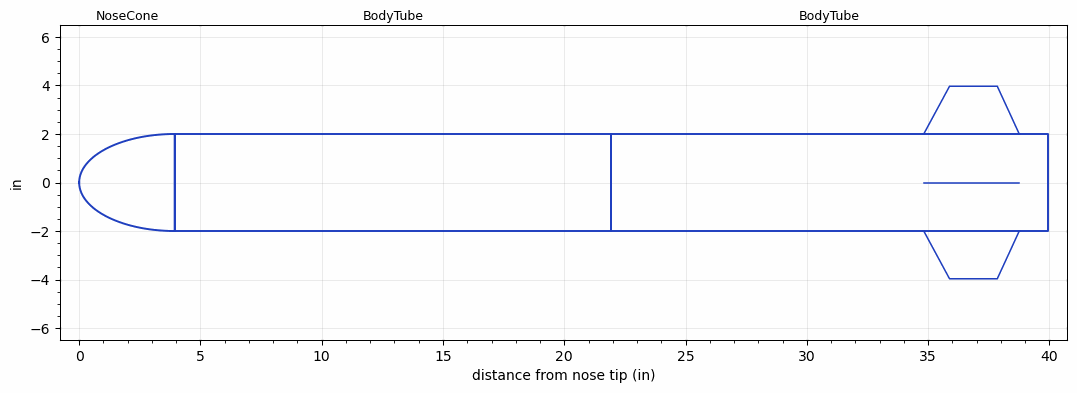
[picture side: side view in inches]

<RASAeroDocument>
 <FileVersion>2</FileVersion>
 <RocketDesign>
  <NoseCone>
   <Length>3.937</Length>
   <Diameter>4</Diameter>
   <Shape>Elliptical</Shape>
   <Location>0</Location>
  </NoseCone>
  <BodyTube>
   <Length>18</Length>
   <Diameter>4</Diameter>
   <Location>3.937</Location>
  </BodyTube>
  <BodyTube>
   <Length>18</Length>
   <Diameter>4</Diameter>
   <Location>21.937</Location>
   <Fin>
    <Count>4</Count>
    <Chord>3.937</Chord>
    <Span>1.9685</Span>
    <SweepDistance>1.063</SweepDistance>
    <TipChord>1.9685</TipChord>
    <Thickness>0.1181</Thickness>
    <Location>5.1181</Location>
    <AirfoilSection>Subsonic NACA</AirfoilSection>
   </Fin>
  </BodyTube>
  <Surface>Smooth (Zero Roughness)</Surface>
  <CD>0</CD>
  <ModifiedBarrowman>False</ModifiedBarrowman>
  <Turbulence>False</Turbulence>
  <UseBooster1>False</UseBooster1>
  <UseBooster2>False</UseBooster2>
 </RocketDesign>
 <LaunchSite>
  <Altitude>0</Altitude>
  <Pressure>29.9214</Pressure>
  <RodAngle>0</RodAngle>
  <RodLength>39.37</RodLength>
  <Temperature>59</Temperature>
  <WindSpeed>4.4739</WindSpeed>
 </LaunchSite>
 <Recovery>
  <Altitude1>0</Altitude1>
  <Altitude2>0</Altitude2>
  <DeviceType1>None</DeviceType1>
  <DeviceType2>None</DeviceType2>
  <Event1>False</Event1>
  <Event2>False</Event2>
  <Size1>0</Size1>
  <Size2>0</Size2>
  <EventType1>None</EventType1>
  <EventType2>None</EventType2>
  <CD1>0</CD1>
  <CD2>0</CD2>
 </Recovery>
 <SimulationList>
  <Simulation>
   <SustainerLaunchWt>2.5577</SustainerLaunchWt>
   <SustainerCG>21.4288</SustainerCG>
   <SustainerIgnitionDelay>0</SustainerIgnitionDelay>
   <Booster1SeparationDelay>0</Booster1SeparationDelay>
   <Booster1IgnitionDelay>0</Booster1IgnitionDelay>
   <IncludeBooster1>False</IncludeBooster1>
   <Booster2Delay>0</Booster2Delay>
   <IncludeBooster2>False</IncludeBooster2>
  </Simulation>
  <Simulation>
   <SustainerLaunchWt>2.5486</SustainerLaunchWt>
   <SustainerCG>21.3819</SustainerCG>
   <SustainerIgnitionDelay>0</SustainerIgnitionDelay>
   <Booster1SeparationDelay>0</Booster1SeparationDelay>
   <Booster1IgnitionDelay>0</Booster1IgnitionDelay>
   <IncludeBooster1>False</IncludeBooster1>
   <Booster2Delay>0</Booster2Delay>
   <IncludeBooster2>False</IncludeBooster2>
  </Simulation>
 </SimulationList>
</RASAeroDocument>
